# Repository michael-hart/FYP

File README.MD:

# Final Year Project
This repo contains all of the code associated with the Final Year Project.
It will mainly just be random blocks of code rather than one continuous project.

## To set up edvs_receiver with FreeRTOS
Download FreeRTOS from the [website](http://www.freertos.org/a00104.html).
From the resulting files, copy the contents of the Source directory to .\FreeRTOS.
Also copy the contents of Demo\Common to .\edvs_receiver\Common.
Open the project workspace using file edvs_receiver/EDVSReceiver.eww.
Compile and run.

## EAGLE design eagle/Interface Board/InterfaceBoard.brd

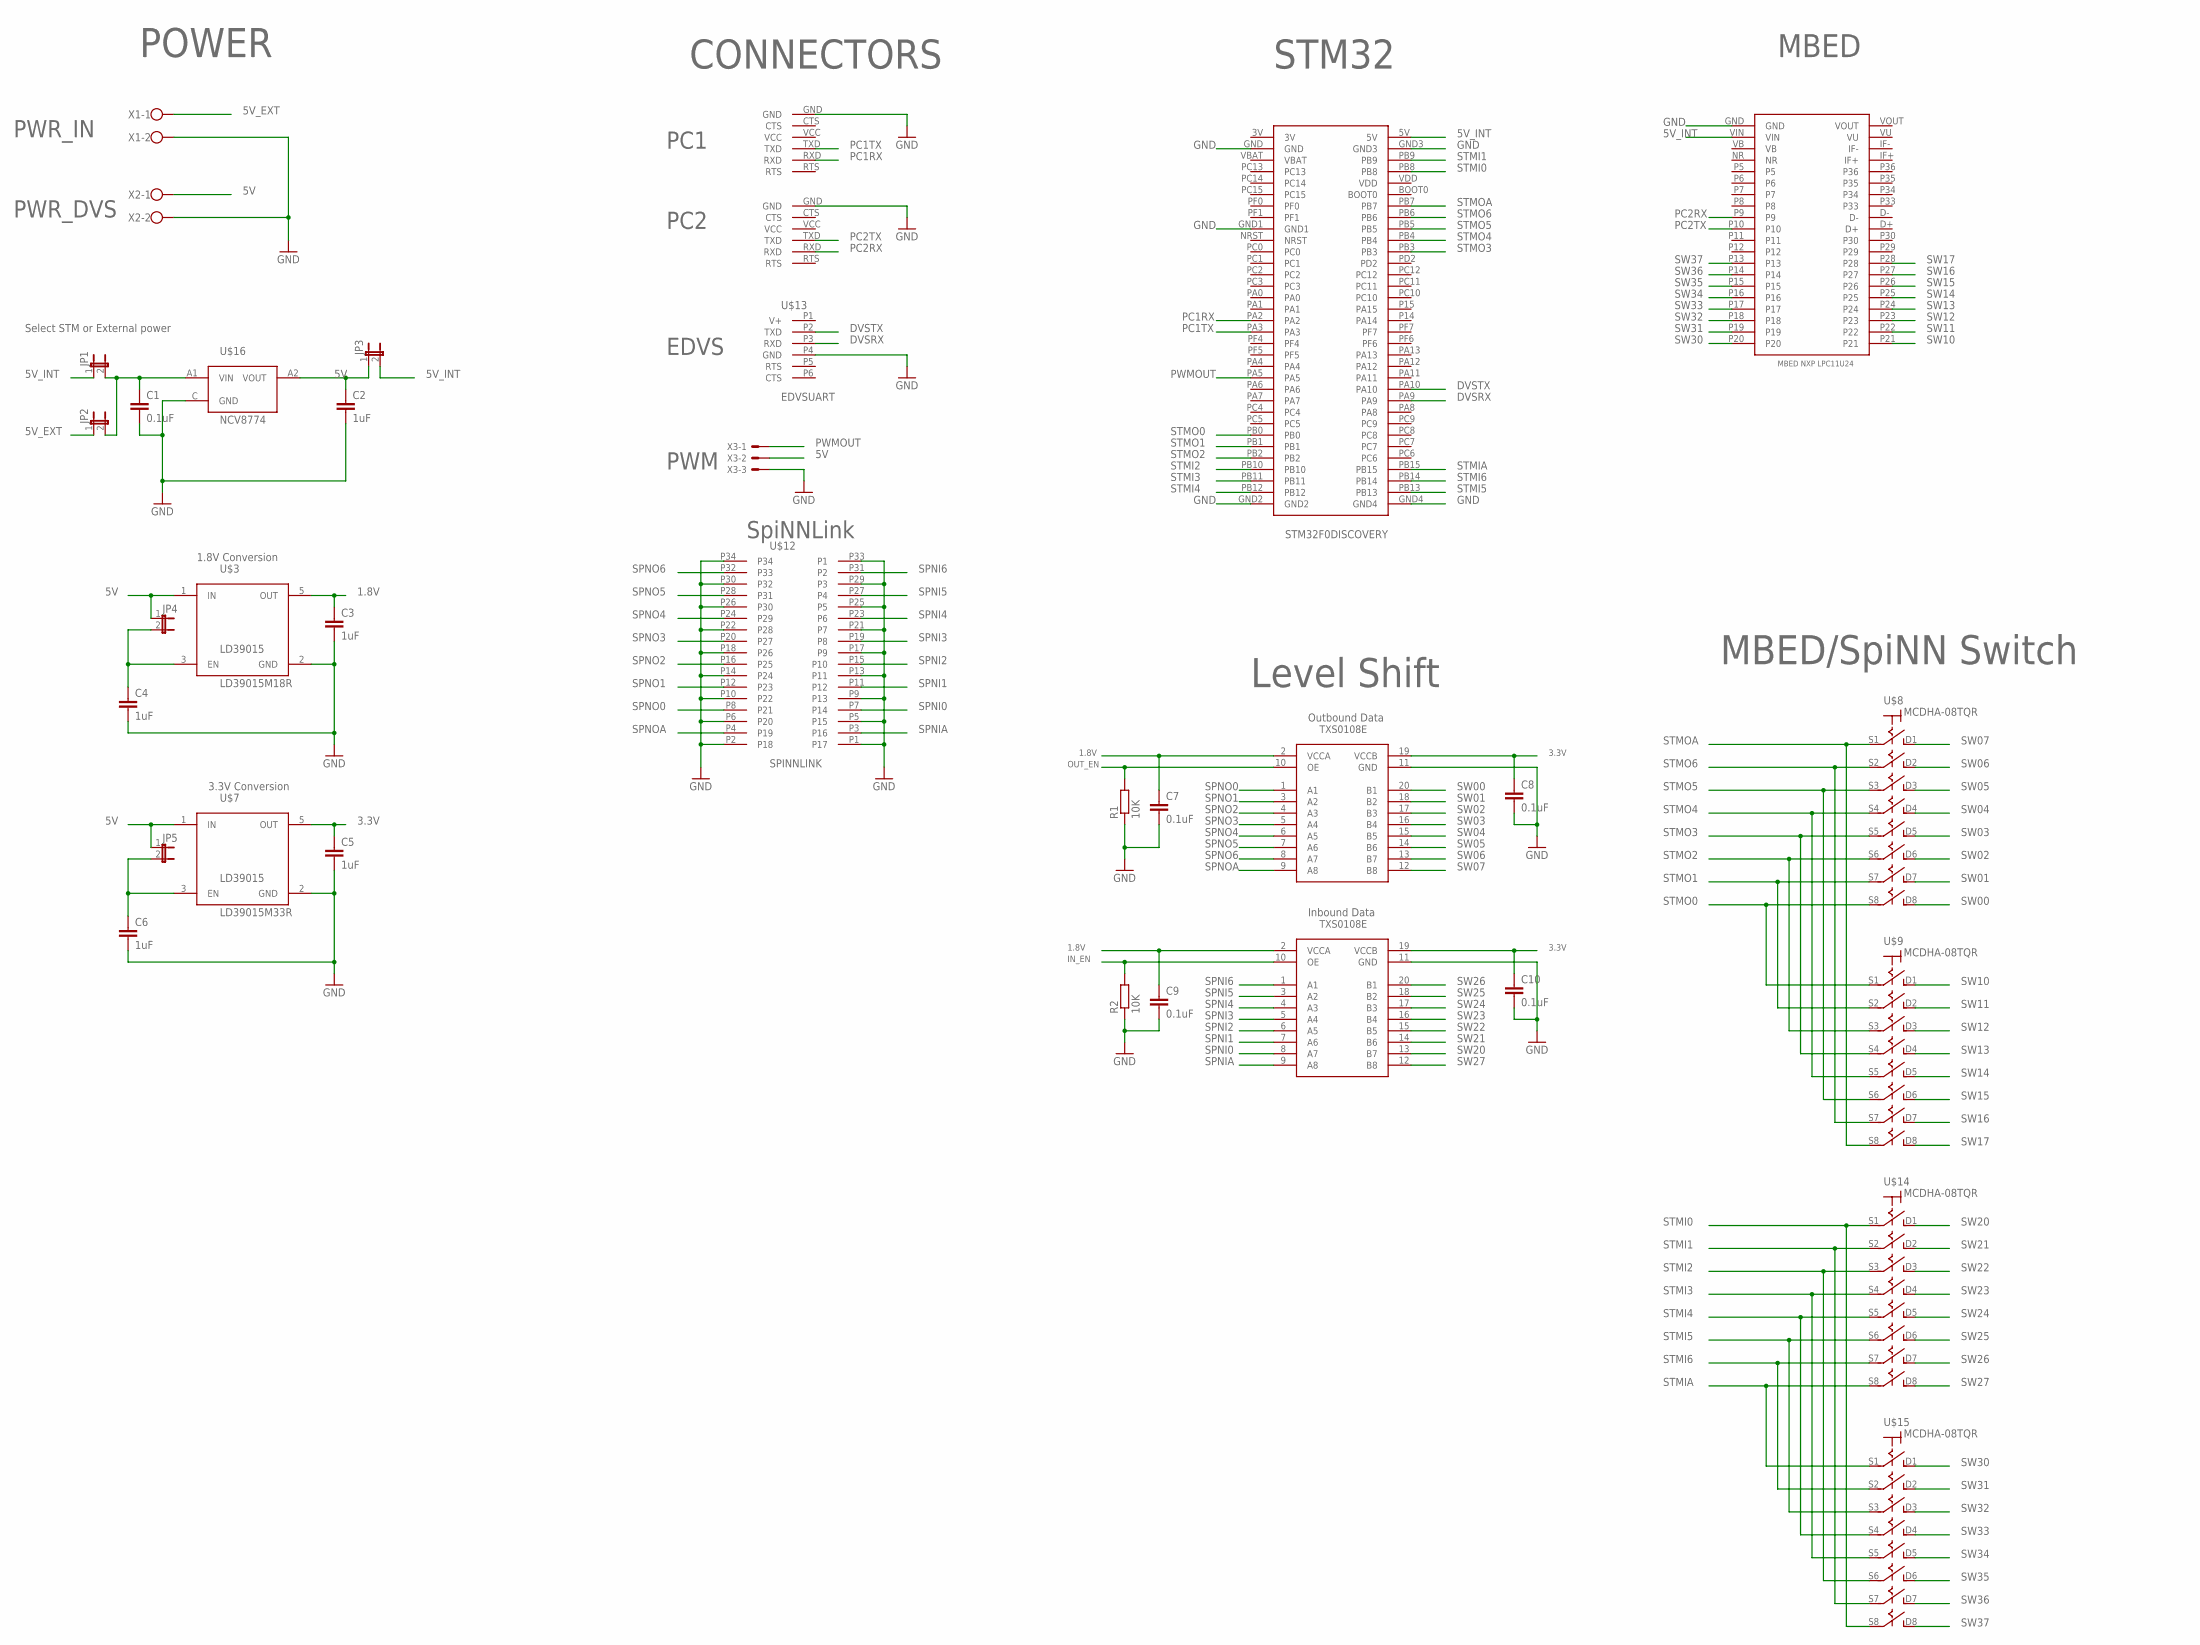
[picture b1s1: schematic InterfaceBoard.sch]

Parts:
C1: 0.1uF; C2.5-3
C2, C3, C4, C5, C6: 1uF; C2.5-3
C7, C8, C9, C10: 0.1uF; C025-025X050
JP1, JP2, JP3, JP4, JP5: JP1E; JP1
R1, R2: 10K; R0805
U$1: STM32F0DISCOVERY
U$3: LD39015M18R; SOT23-5L
U$4: LPC11U24
U$5, U$6: TXS0108EPWR; TSSOP20
U$7: LD39015M33R; SOT23-5L
U$8, U$9, U$14, U$15: MCDHA-08TQR; DIPSWITCH8
U$10, U$11: FTDI; FTDIHEADER
U$12: SPINNLINK; C42A
U$13: EDVSUART; MICROMATCH8
U$16: NCV8774; DPACK_3
X1, X2: W237-102
X3: KK-156-3

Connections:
1.8V: C3.1, C7.1, C9.1, U$3.5 (OUT), U$5.2 (VCCA), U$6.2 (VCCA)
3.3V: C5.1, C8.1, C10.1, U$5.19 (VCCB), U$6.19 (VCCB), U$7.5 (OUT)
5V: C2.1, JP3.1, JP4.1, JP5.1, U$3.1 (IN), U$7.1 (IN), U$16.A2 (VOUT), X2.1, X3.2
5V_EXT: JP2.1, X1.1
5V_INT: JP1.1, JP3.2, U$1.5V, U$4.VIN
DVSRX: U$1.PA9, U$13.P3 (RXD)
DVSTX: U$1.PA10, U$13.P2 (TXD)
GND: C1.2, C2.2, C3.2, C4.2, C5.2, C6.2, C7.2, C8.2, C9.2, C10.2, R1.1, R2.1, U$1.GND, U$1.GND1, U$1.GND2, U$1.GND3, U$1.GND4, U$3.2 (GND), U$4.GND, U$5.11 (GND), U$6.11 (GND), U$7.2 (GND), U$10.GND, U$11.GND, U$12.P1 (P17), U$12.P2 (P18), U$12.P5 (P15), U$12.P6 (P20), U$12.P9 (P13), U$12.P10 (P22), U$12.P13 (P11), U$12.P14 (P24), U$12.P17 (P9), U$12.P18 (P26), U$12.P21 (P7), U$12.P22 (P28), U$12.P25 (P5), U$12.P26 (P30), U$12.P29 (P3), U$12.P30 (P32), U$12.P33 (P1), U$12.P34, U$13.P4 (GND), U$16.C (GND), X1.2, X2.2, X3.3
IN_EN: R2.2, U$6.10 (OE)
unnamed: C1.1, JP1.2, JP2.2, U$16.A1 (VIN)
unnamed: C4.1, JP4.2, U$3.3 (EN)
unnamed: C6.1, JP5.2, U$7.3 (EN)
OUT_EN: R1.2, U$5.10 (OE)
PC1RX: U$1.PA2, U$10.RXD
PC1TX: U$1.PA3, U$10.TXD
PC2RX: U$4.P9, U$11.RXD
PC2TX: U$4.P10, U$11.TXD
PWMOUT: U$1.PA5, X3.1
SPNI0: U$6.8 (A7), U$12.P7 (P14)
SPNI1: U$6.7 (A6), U$12.P11 (P12)
SPNI2: U$6.6 (A5), U$12.P15 (P10)
SPNI3: U$6.5 (A4), U$12.P19 (P8)
SPNI4: U$6.4 (A3), U$12.P23 (P6)
SPNI5: U$6.3 (A2), U$12.P27 (P4)
SPNI6: U$6.1 (A1), U$12.P31 (P2)
SPNIA: U$6.9 (A8), U$12.P3 (P16)
SPNO0: U$5.1 (A1), U$12.P8 (P21)
SPNO1: U$5.3 (A2), U$12.P12 (P23)
SPNO2: U$5.4 (A3), U$12.P16 (P25)
SPNO3: U$5.5 (A4), U$12.P20 (P27)
SPNO4: U$5.6 (A5), U$12.P24 (P29)
SPNO5: U$5.7 (A6), U$12.P28 (P31)
SPNO6: U$5.8 (A7), U$12.P32 (P33)
SPNOA: U$5.9 (A8), U$12.P4 (P19)
STMI0: U$1.PB8, U$14.S1, U$15.S8
STMI1: U$1.PB9, U$14.S2, U$15.S7
STMI2: U$1.PB10, U$14.S3, U$15.S6
STMI3: U$1.PB11, U$14.S4, U$15.S5
STMI4: U$1.PB12, U$14.S5, U$15.S4
STMI5: U$1.PB13, U$14.S6, U$15.S3
STMI6: U$1.PB14, U$14.S7, U$15.S2
STMIA: U$1.PB15, U$14.S8, U$15.S1
STMO0: U$1.PB0, U$8.S8, U$9.S1
STMO1: U$1.PB1, U$8.S7, U$9.S2
STMO2: U$1.PB2, U$8.S6, U$9.S3
STMO3: U$1.PB3, U$8.S5, U$9.S4
STMO4: U$1.PB4, U$8.S4, U$9.S5
STMO5: U$1.PB5, U$8.S3, U$9.S6
STMO6: U$1.PB6, U$8.S2, U$9.S7
STMOA: U$1.PB7, U$8.S1, U$9.S8
SW00: U$5.20 (B1), U$8.D8
SW01: U$5.18 (B2), U$8.D7
SW02: U$5.17 (B3), U$8.D6
SW03: U$5.16 (B4), U$8.D5
SW04: U$5.15 (B5), U$8.D4
SW05: U$5.14 (B6), U$8.D3
SW06: U$5.13 (B7), U$8.D2
SW07: U$5.12 (B8), U$8.D1
SW10: U$4.P21, U$9.D1
SW11: U$4.P22, U$9.D2
SW12: U$4.P23, U$9.D3
SW13: U$4.P24, U$9.D4
SW14: U$4.P25, U$9.D5
SW15: U$4.P26, U$9.D6
SW16: U$4.P27, U$9.D7
SW17: U$4.P28, U$9.D8
SW20: U$6.13 (B7), U$14.D1
SW21: U$6.14 (B6), U$14.D2
SW22: U$6.15 (B5), U$14.D3
SW23: U$6.16 (B4), U$14.D4
SW24: U$6.17 (B3), U$14.D5
SW25: U$6.18 (B2), U$14.D6
SW26: U$6.20 (B1), U$14.D7
SW27: U$6.12 (B8), U$14.D8
SW30: U$4.P20, U$15.D1
SW31: U$4.P19, U$15.D2
SW32: U$4.P18, U$15.D3
SW33: U$4.P17, U$15.D4
SW34: U$4.P16, U$15.D5
SW35: U$4.P15, U$15.D6
SW36: U$4.P14, U$15.D7
SW37: U$4.P13, U$15.D8

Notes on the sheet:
STM32
POWER
PWR_IN
PWR_DVS
Select STM or External power
1.8V Conversion
MBED
Level Shift
3.3V Conversion
Outbound Data
Inbound Data
MBED/SpiNN Switch
CONNECTORS
PC1
PC2
EDVS
PWM
SpiNNLink

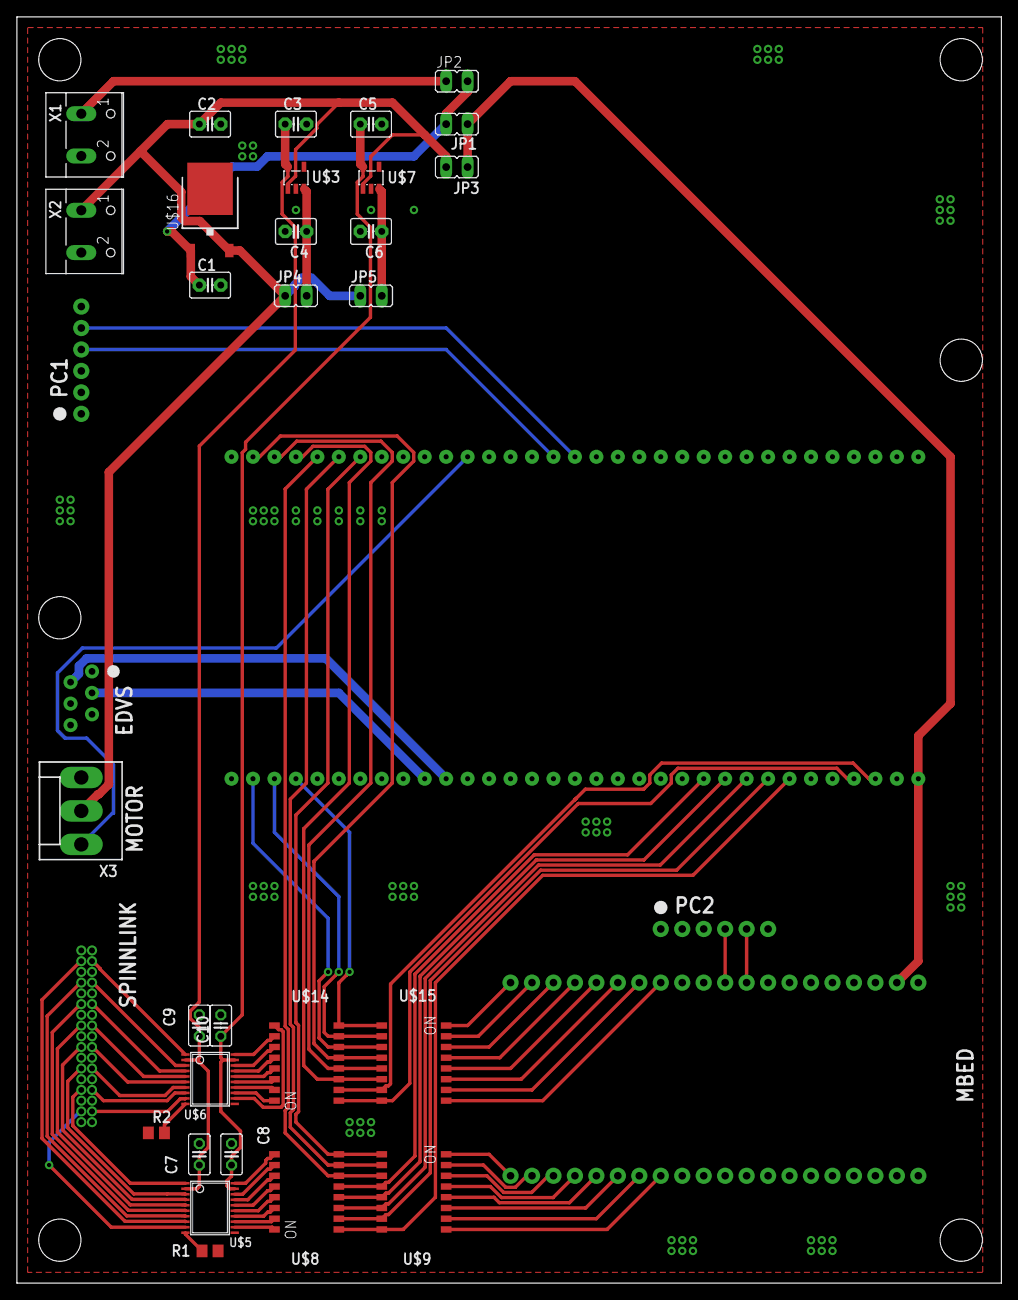
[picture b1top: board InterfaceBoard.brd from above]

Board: 2 copper layers, 116.5 x 149.8 mm, 35 parts (0 on the bottom side), 82 nets.

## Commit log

2016-11-09 Add readme and gitignore
2016-11-09 Added logging as in HCR and updated gitignore
2016-11-09 Added untested support for serial object
2016-11-20 Added threaded reading and writing to/from edvs
    Uses standard serial threading library objects with overrides.
    Uses logging as normal to write messages to the screen.
    Changed baud rate to 115200.
    Only uses second COM port; no option to specify port
2016-11-25 Added config file for easier changing of baud rate
2016-11-25 Added code for understanding events including config and listeners
2016-11-25 PEP8
2016-11-25 Modifications to decoding method
2016-11-29 Added relative path for config file and PEP8 fixes
2016-11-29 Added state variable
2016-11-30 Added panel that redraws in a thread upon receiving events
2017-05-04 Initial Commit of board test Python project
2017-05-04 EDVS driver changes to buffer reading (not working)
2017-05-04 Add template FreeRTOS project ready for updates
2017-05-04 Rearranged project files and added README instructions
2017-05-15 Update to use new main files and templates
    Build process uses build_flash.bat
    Start of USART code has been written
2017-05-15 Remove unnecessary chip erase
2017-05-15 Removed deleted project files
2017-05-15 Upgrade to flash script to start application
2017-05-15 Changed baud rate
2017-05-15 Added watchdog and start of USART functionality
2017-05-16 Updates to PC serial comms
    Commands now terminated with \r
    Baud rate set to 1M
    Controller.py accepts echoed bytes
2017-05-16 Echo supported
2017-05-16 Added test files for automated testing and adjusted baud rate
2017-05-16 Switched PC comms to USART2 and remove comments
2017-05-16 Rename file and documentation added
2017-05-16 Minor renames of variables and added non-functional DVS code
2017-05-16 Move code into main function
2017-05-16 First attempt at forwarding DVS packets, untested
2017-05-16 Added DVS tests and corrections to get commands working
2017-05-17 Modified semaphore use to lock instead of semaphore
2017-05-17 Added spinn start and missing header guard definition lines
2017-05-18 Updated test system to be more robust
2017-05-18 Added commands to be sent from PC to board
2017-05-18 Modified UART interaction to include error messages and handling
2017-05-18 Fix bug where stopping inactive timer waits indefinitely
2017-05-18 Fix divide error in timer period change
2017-05-18 Rename DVS tests
2017-05-18 Remove utf-8 to avoid encoding errors
2017-05-18 Added \r to echo tests ready to fix bug
2017-05-18 Allow \r inside messages and add use_dvs function to controller
2017-05-18 Added methods to allow simulated DVS data to be placed into buffer
2017-05-18 Added tests and fixed bugs for some SpiNN functionality
2017-05-18 Added Python code for 2-of-7 encoding with passing tests
2017-05-18 Changed log calls to use %s to avoid lint errors
2017-05-19 New file from generator with same clock attributes
2017-05-19 Added ctags files to gitignore
2017-05-19 Added GPIO support [untested] and added simple test for crash
2017-05-19 Added start of MBED tests and minor tidying
2017-05-19 Added duration to MBED messages
2017-05-19 Increased test set including timing tests + minor tidying and import error fix
2017-05-20 Configured interrupts for acknowledge pin
2017-05-21 Added tests for encoding DVS packets and fixes to encode algorithm
2017-05-21 Better error handling on controllers
2017-05-21 Corrected C-version of SpiNNaker encoding
2017-05-21 Removed debug print statement
2017-05-22 Removed false import from template
2017-05-22 Add methods and test for SpiNNaker link although interrupt is broken
2017-05-22 Added interrupt files, corrected priorities and interrupt use
    Interrupts moved to separate file stm32f0xx_it.c
    File uses externed semaphore to give from ISR
    Added hard fault handler currently not used
2017-05-23 Modified to fix multiple packet sending
    Bug fixed where false flag prevented reading the queue
    Added count parameter on gspn on both MBED, controller, and tests
    Changed buffer sizes and priorities as required
2017-05-23 Modified local variables to be static
2017-05-23 Minor renaming of functions
2017-05-24 Storing bitpacked algorithm in new branch as it is broken
2017-05-24 Changed downsizing algorithm to use less memory
2017-05-24 Changed to correct mode calculations and added 32x32 tests
2017-05-25 Updated tests and buffer length to ensure all tests pass
2017-05-27 Change to memory map file seems to allow larger arrays in compilation
2017-06-17 Modified test set to include device options on command line
2017-06-17 Changed baud rate to 500K and updated to be compatible with python3
2017-06-17 Updated dvs send_string function and modified queue behaviour to prevent overflow
2017-06-17 Added test to check that various values are received from DVS
2017-06-19 Added all code and tests for inbound SpiNNaker link
2017-06-19 Update incorrect starting port value
2017-06-19 Added support for level shift enable signals and minor tidy
2017-06-19 Corrected bad ORing of new port value
2017-06-19 Added missing source files and added test results
    Test results obtained by using batch script full_run.bat
    Missing files are EAGLE project files and main.cpp for MBED
2017-06-20 Added missing system reset line with updated results to compensate
